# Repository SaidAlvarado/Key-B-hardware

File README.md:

# Key-B keyboard
ZMK based wireless half keyboard

Remember to attribute: https://github.com/daprice/keyswitches.pretty/tree/master

Attribute the Fanstel module footprint and symbols to: https://github.com/hemalchevli/Fanstel-kicad-library

## Battery
- [Big Option](https://www.amazon.fr/EEMB-Batterie-polym%C3%A8re-Rechargeable-connecteur/dp/B09DPPP8ZV/)
  - JST Connector (PH). [Digikey Link](https://www.amazon.fr/EEMB-Batterie-polym%C3%A8re-Rechargeable-connecteur/dp/B09DPPP8ZV/?th=1)
- [Slightly smaller option](https://www.amazon.fr/EEMB-Batterie-Rechargeable-Navigation-Enregistreur/dp/B08FD3V6TF)
- Charging current
  - std 0.2C, max. 1C. (60mA to 300mA)

## BOM

- Premade digikey cart: https://www.digikey.fr/short/4dtv58d8

## References

#### Crystal oscillator design
- [General nRF crystal design guidelines](https://devzone.nordicsemi.com/guides/hardware-design-test-and-measuring/b/nrf5x/posts/general-pcb-design-guidelines-for-nrf52)
- [nRF52840 reference circuit](https://infocenter.nordicsemi.com/index.jsp?topic=%2Fps_nrf52840%2Fref_circuitry.html)
  - They recommend a 9pF crystal for the 32.768kHz crystal
- [Nordic White paper on Crystal oscillator design](https://infocenter.nordicsemi.com/pdf/nwp_015.pdf?cp=12_12) Note, there is a correction of this white paper on the first link in this section.

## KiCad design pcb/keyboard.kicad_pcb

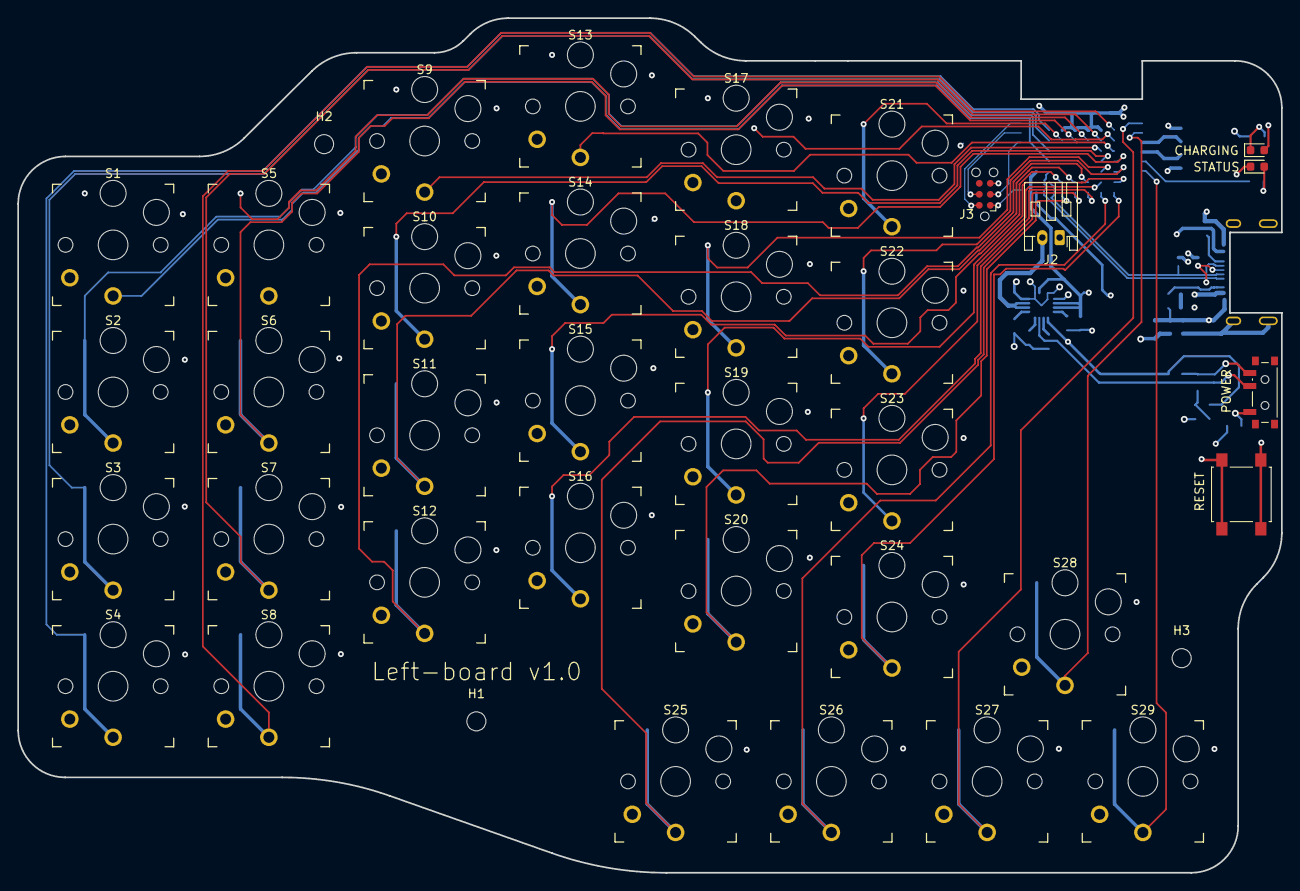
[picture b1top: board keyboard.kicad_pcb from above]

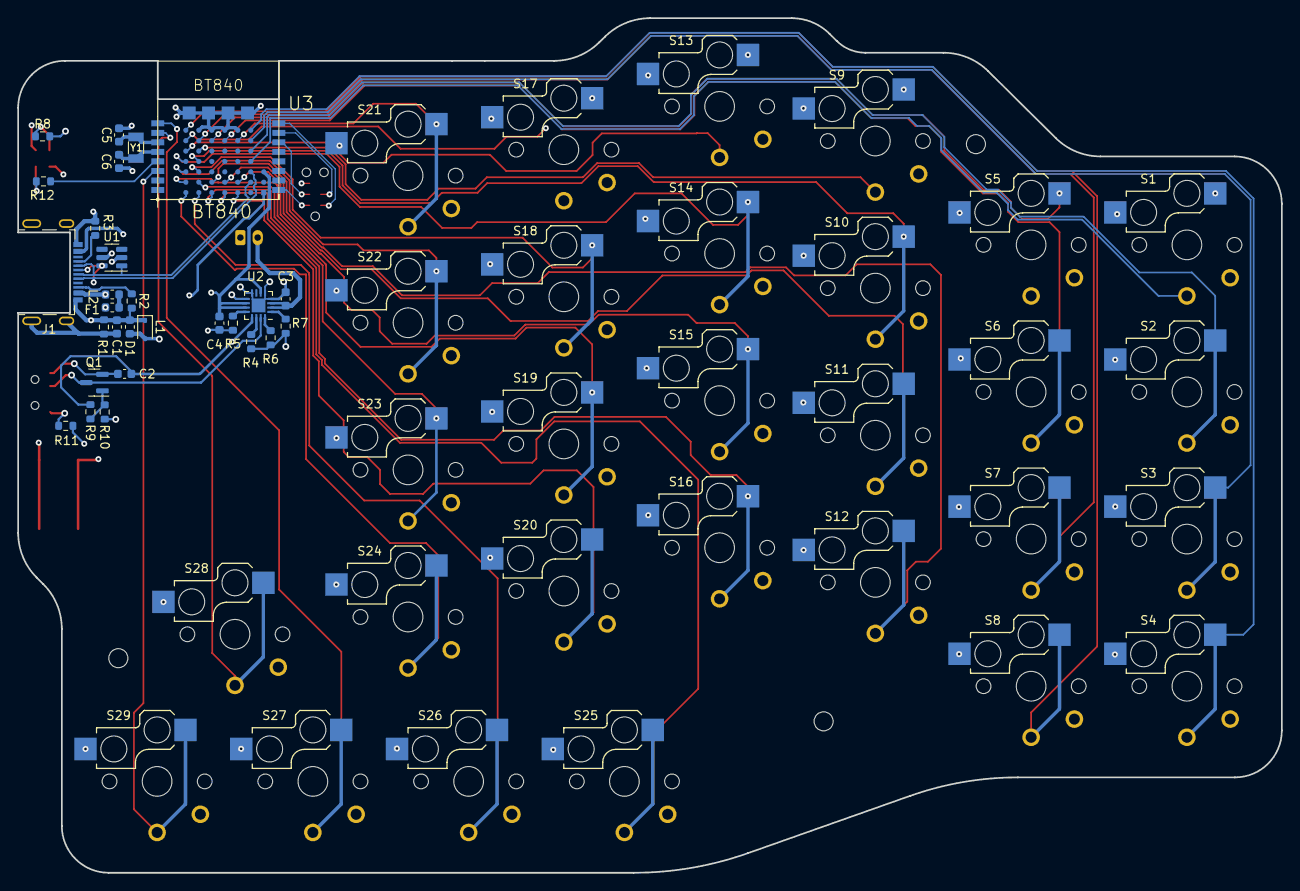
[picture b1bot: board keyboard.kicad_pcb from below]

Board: 4 copper layers, 146.0 x 98.8 mm, 66 parts (28 on the bottom side), 58 nets.

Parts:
C1: 100 nF; C_0603_1608Metric
C2, C3, C4: 4.7 uF; C_0603_1608Metric
C5, C6: 12pF; C_0603_1608Metric
D1: STS321050B100; D_SOD-323
F1: ERB-RE0R75V; Fuse_0603_1608Metric
H1, H2, H3: MountingHole; MountingHole_2.2mm_M2
J1: USB4510-03-1-A; USB_C_Receptacle_GCT_USB4510-03-1-A
J2: Battery; JST_PH_S2B-PH-K_1x02_P2.00mm_Horizontal
J3: Tag-Connect TC2030; Tag-Connect_TC2030-IDC-NL_2x03_P1.27mm_Vertical
L1, L2: BLM18SG121TN1D; L_0603_1608Metric
LED1: orange; LED_0603_1608Metric
LED2: green; LED_0603_1608Metric
Q1: 2N7002; SOT-23
R1: 1 MOhm; R_0603_1608Metric
R2, R3: 5.1 kOhm; R_0603_1608Metric
R4: 47 kOhm; R_0603_1608Metric
R5, R8: 1.5 kOhm; R_0603_1608Metric
R6: 5.6 kOhm; R_0603_1608Metric
R7, R10: 10 kOhm; R_0603_1608Metric
R9: 100 Ohm; R_0603_1608Metric
R11: 100 kOhm; R_0603_1608Metric
R12: 470 Ohm; R_0603_1608Metric
S1, S2, S3, S4, S5, S6, S7, S8, S9, S10, S11, S12, S13, S14, S15, S16, S17, S18, S19, S20, S21, S22, S23, S24, S25, S26, S27, S28, S29: Kailh_socket_PG1350_optional
SW1: PWR; SW_SPDT_PCM12
SW2: Reset; SW_SPST_B3S-1000
U1: SRV05-4; SOT-23-6
U2: BQ24075; VQFN-16-1EP_3x3mm_P0.5mm_EP1.6x1.6mm
U3: BT840; Fanstel_BT840
Y1: ECS-.327-9-34B-TR; Crystal_SMD_3215-2Pin_3.2x1.5mm

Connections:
+5V: C2.1, F1.2, R9.1, U1.5 (VP), U2.13 (IN), U3.F6 (VBUS)
+BATT: C3.1, J2.2, R11.2, U2.2 (BAT), U2.3 (BAT)
+VSW: C4.1, LED1.2 (A), U2.6 (EN1), U2.10 (OUT), U2.11 (OUT), U3.F4 (VDDH)
Earth: C1.2, J1.S1 (SHIELD), R1.1
GND: C2.2, C3.2, C4.2, C5.1, C6.1, D1.2 (A2), J2.1, J3.5, L1.2, LED2.1 (K), Q1.2 (S), R4.2, R5.2, R6.2, R7.2, R10.2, S1.2, S2.2, S3.2, S4.2, S5.2, S6.2, S7.2, S8.2, S9.2, S10.2, S11.2, S12.2, S13.2, S14.2, S15.2, S16.2, S17.2, S18.2, S19.2, S20.2, S21.2, S22.2, S23.2, S24.2, S25.2, S26.2, S27.2, S28.2, S29.2, SW1.3 (C), SW2.2, U1.2 (VN), U2.4 (~CE), U2.5 (EN2), U2.8 (VSS), U2.17 (VSS), U3.A0 (VSS1), U3.B0 (VSS2), U3.C0 (VSS3), U3.D0 (VSS4), U3.F0 (GND), U3.F1 (GND), U3.F2 (GND), U3.F3 (GND)
GNDPWR: C1.1, D1.1 (A1), J1.A1 (GND), J1.A12 (GND), J1.B1 (GND), J1.B12 (GND), L1.1, R1.2, R2.1, R3.1
unnamed: F1.1, L2.2
unnamed: J1.A5 (CC1), R3.2
unnamed: J1.B5 (CC2), R2.2
unnamed: LED1.1 (K), R8.1
unnamed: LED2.2 (A), R12.2
unnamed: Q1.1 (G), R9.2, R10.1
unnamed: R11.1, SW1.1 (A)
unnamed: R5.1, U2.12 (ILIM)
unnamed: R6.1, U2.16 (ISET)
unnamed: R4.1, U2.14 (TMR)
unnamed: R7.1, U2.1 (TS)
unnamed: R8.2, U2.9 (~CHG)
unnamed: C5.2, U3.3 (P0.00/XL1), Y1.2
unnamed: C6.2, U3.4 (P0.01/XL2), Y1.1
unnamed: R12.1, U3.5 (P0.02/AIN0)
P0.03: S29.1, U3.6 (P0.03/AIN1)
P0.04: S10.1, U3.A3 (P0.04)
P0.05: S18.1, U3.A4 (P0.05)
P0.07: S23.1, U3.A5 (P0.07)
P0.08: S12.1, U3.B5 (P0.08)
P0.20: S3.1, U3.E1 (P0.20)
P0.21: S2.1, U3.E2 (P0.21)
P0.23: S21.1, U3.D1 (P0.23)
P0.24: S6.1, U3.C1 (P0.24)
P0.25: S5.1, U3.B1 (P0.25)
P0.26: S27.1, U3.1 (P0.26/SDA)
P0.27: S28.1, U3.2 (P0.27/SCL)
P0.28: S7.1, U3.A1 (P0.28)
P0.29: S9.1, U3.A2 (P0.29)
P1.01: S15.1, U3.D5 (P1.01)
P1.02: S11.1, U3.C5 (P1.02)
P1.03: S16.1, U3.B6 (P1.03)
P1.04: S25.1, U3.C6 (P1.04)
P1.05: S20.1, U3.D6 (P1.05)
P1.06: S24.1, U3.Z6 (P1.06)
P1.07: S4.1, U3.E0 (P1.07)
P1.08: S26.1, U3.A6 (P1.08)
P1.09: S1.1, U3.E3 (P1.09)
P1.10: S19.1, U3.Z5 (P1.10)
P1.11: S8.1, U3.Z0 (P1.11)
P1.12: S17.1, U3.Z1 (P1.12)
P1.13: S13.1, U3.Z2 (P1.13)
P1.14: S14.1, U3.Z3 (P1.14)
P1.15: S22.1, U3.Z4 (P1.15)
RESET: J3.3, SW2.1, U3.14 (P0.18/RESET)
SWDCLK: J3.4, U3.15 (SWCLK)
SWDIO: J3.2, U3.16 (SWDIO)
SYSOFF: Q1.3 (D), SW1.2 (B), U2.15 (SYSOFF)
USB-D+: J1.A6 (D+), J1.B6 (D+), U1.6 (IO4), U3.E4 (D+)
USB-D-: J1.A7 (D-), J1.B7 (D-), U1.1 (IO1), U3.E5 (D-)
VBUS: J1.A4 (VBUS), J1.A9 (VBUS), J1.B4 (VBUS), J1.B9 (VBUS), L2.1
VDD: J3.1, U3.9 (VDD)

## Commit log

2023-12-07 #1 add battery management and USB socket schematics
2023-12-08 #1 add symbol and footprint for BT840
2023-12-08 #1 fix errors on the BT840 symbol and footprint
2023-12-08 #1 Add preliminary switch connections on the schematic
2023-12-11 #1 Change USB connector components to Digikey 0603
2023-12-15 fix - Add temporary .lck files to gitignore
2023-12-15 #1 Choose/calculate 32khz crystal. Change all Caps and Res to 0603
2023-12-15 Add #Autosavefile# to .gitignore
2023-12-15 #1 Add crystal circuit design references to the ReadMe
2023-12-16 #1 Select Battery and Battery Connector
2023-12-16 #1 Select power switch
2023-12-16 #1 Select reset switch and LED
2023-12-16 #1 Mark nRF unconnected pins
2023-12-16 #1 Complete BOM information
2023-12-16 #1 Reorganize the schematic
2023-12-16 #1 Reassign component references
2023-12-16 #2 Import schematic components to the PCB
2023-12-20 #2 add JLCPCB design rules
2023-12-20 #2 add pcb outline,roughly place components
2023-12-23 #2 Expand the PCB to accomodate all components
2023-12-23 #2 route charging circuit, part 1
2023-12-24 #2 route USB-C connector + diff pair
2023-12-25 #2 route all the buttons
2024-01-06 #2 Add mounting holes
2024-01-06 #2 Add silkscreen names to buttons, leds and version
2024-01-07 #3 Complete BOM on Kicad schamatic and make digikey cart
2024-01-07 #3 Add a full cost-breakdown in a Markdown file
2024-01-07 #3 Add descriptive comment to the CSV to Markdown table script
2024-01-14 fix: change USB footprint to comply with 0.3mm copper-to-edge constraint
2024-01-14 Generate gerber files for JLCPCB
2024-01-14 #4 add first iteration of the key layout
2024-02-25 Update keyboard name
2024-02-25 Update Name again
2024-02-25 Typo in fix me
2024-03-01 upgrade project to kicad 8
2024-03-03 #5 add 3d models for the switches + keycaps
2024-03-04 #5 add USB-C receptacle 3D model
2024-03-04 #5 link usb connector model to the footprint library
2024-03-20 #5 Add model for reset button
2024-03-20 #5 Add BT840 3D model
2024-03-20 #5 Add battery charger 3D model
2024-03-22 #6 Add full step 3d model
